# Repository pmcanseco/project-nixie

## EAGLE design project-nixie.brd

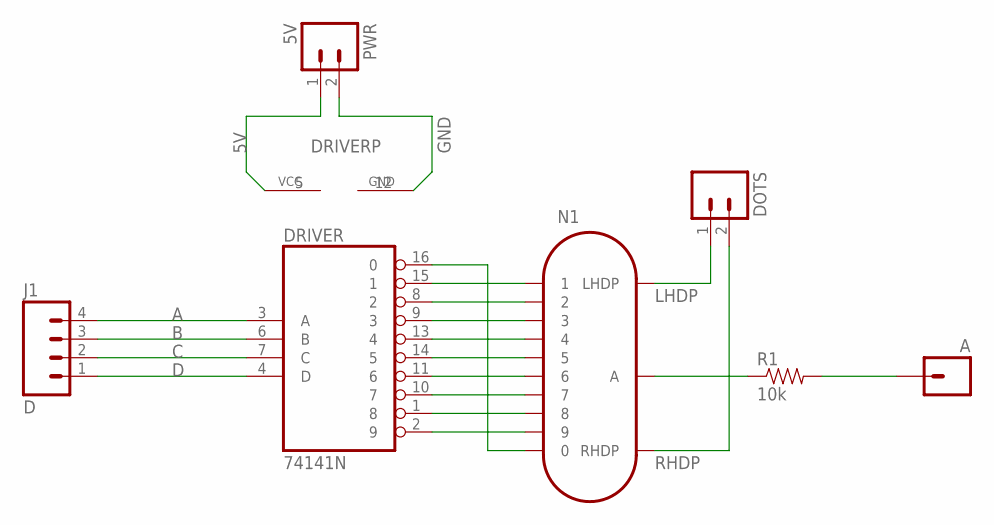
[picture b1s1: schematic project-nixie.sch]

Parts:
A: M01PTH; 1X01
DOTS: M02PTH; 1X02
DRIVER: 74141N; DIL16
J1: D; 1X04_LOCK
N1: IN-16
PWR: 5V; 1X02_LOCK
R1: 10k; AXIAL-0.3

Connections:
5V: DRIVER.5 (VCC), PWR.1
A: DRIVER.3 (A), J1.4
B: DRIVER.6 (B), J1.3
C: DRIVER.7 (C), J1.2
D: DRIVER.4 (D), J1.1
GND: DRIVER.12 (GND), PWR.2
LHDP: DOTS.1, N1.LHDP
unnamed: DRIVER.2 (9), N1.9
unnamed: DRIVER.1 (8), N1.8
unnamed: DRIVER.10 (7), N1.7
unnamed: DRIVER.11 (6), N1.6
unnamed: DRIVER.14 (5), N1.5
unnamed: DRIVER.13 (4), N1.4
unnamed: DRIVER.9 (3), N1.3
unnamed: DRIVER.8 (2), N1.2
unnamed: DRIVER.15 (1), N1.1
unnamed: DRIVER.16 (0), N1.0
unnamed: N1.A, R1.P$1 (1)
unnamed: A.1, R1.P$2 (2)
RHDP: DOTS.2, N1.RHDP

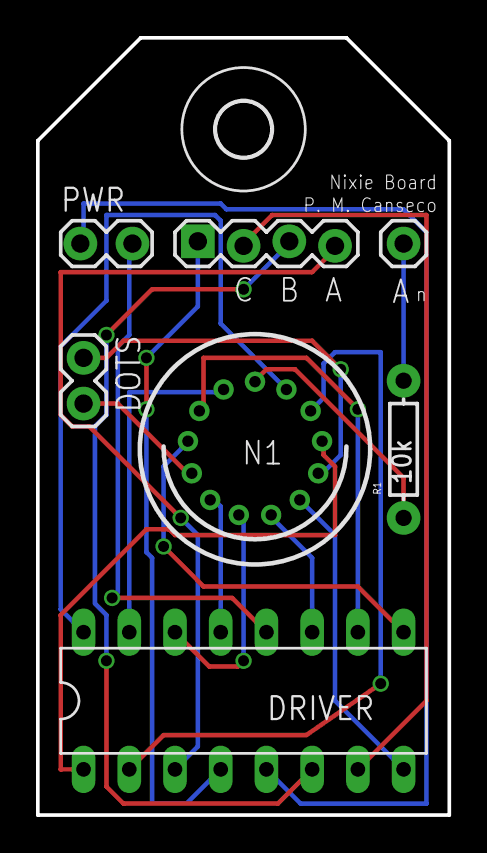
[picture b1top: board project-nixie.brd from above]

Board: 2 copper layers, 22.9 x 43.2 mm, 8 parts (0 on the bottom side), 20 nets.

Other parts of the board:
U$1: 3,0

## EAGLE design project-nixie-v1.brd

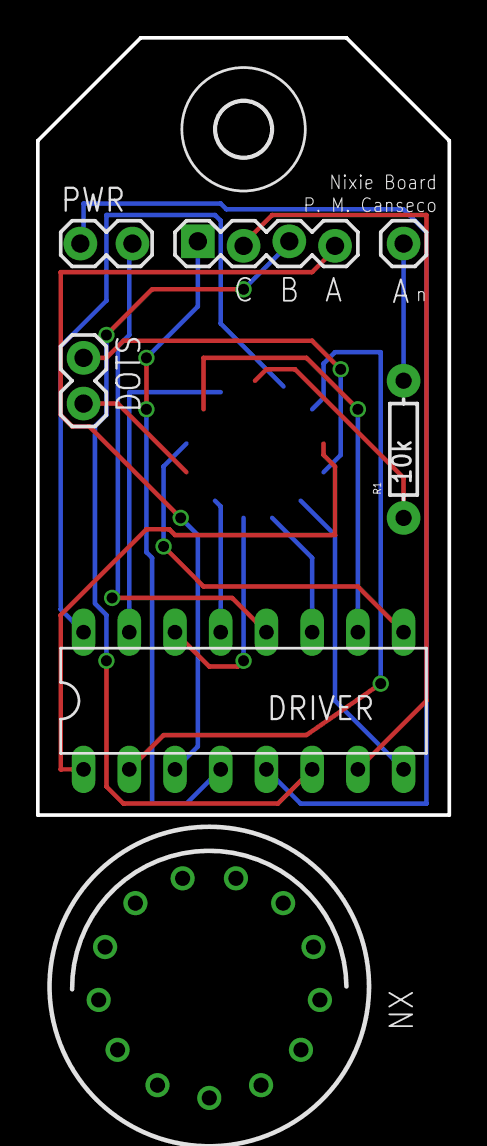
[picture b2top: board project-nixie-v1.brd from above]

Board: 2 copper layers, 22.9 x 43.2 mm, 8 parts (0 on the bottom side), 20 nets.

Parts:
A: 1X01
DOTS: 1X02
DRIVER: 74141N; DIL16
J1: D; 1X04_LOCK
NX: IN-14
PWR: 5V; 1X02_LOCK
R1: 10k; AXIAL-0.3
U$1: 3,0

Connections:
5V: DRIVER.5, PWR.1
A: DRIVER.3, J1.4
B: DRIVER.6, J1.3
C: DRIVER.7, J1.2
D: DRIVER.4, J1.1
GND: DRIVER.12, PWR.2
LHDP: DOTS.1, NX.LHDP
unnamed: DRIVER.2, NX.9
unnamed: DRIVER.1, NX.8
unnamed: DRIVER.10, NX.7
unnamed: DRIVER.11, NX.6
unnamed: DRIVER.14, NX.5
unnamed: DRIVER.13, NX.4
unnamed: DRIVER.9, NX.3
unnamed: DRIVER.8, NX.2
unnamed: DRIVER.15, NX.1
unnamed: DRIVER.16, NX.0
unnamed: NX.A, R1.P$1
unnamed: A.1, R1.P$2
RHDP: DOTS.2, NX.RHDP

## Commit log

2016-06-18 initial upload
2016-06-18 changed to single-tube breakout
2016-06-20 re-upload to seeed
2016-07-10 initial arduino code upload
2016-07-16 version 2 of the board
2018-01-14 finalized arduino firmware, added documentation and plate models.

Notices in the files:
parts and their libraries:
SparkFun-Connectors: Licensing: Creative Commons ShareAlike 4.0 International - https://creativecommons.org/licenses/by-sa/4.0
